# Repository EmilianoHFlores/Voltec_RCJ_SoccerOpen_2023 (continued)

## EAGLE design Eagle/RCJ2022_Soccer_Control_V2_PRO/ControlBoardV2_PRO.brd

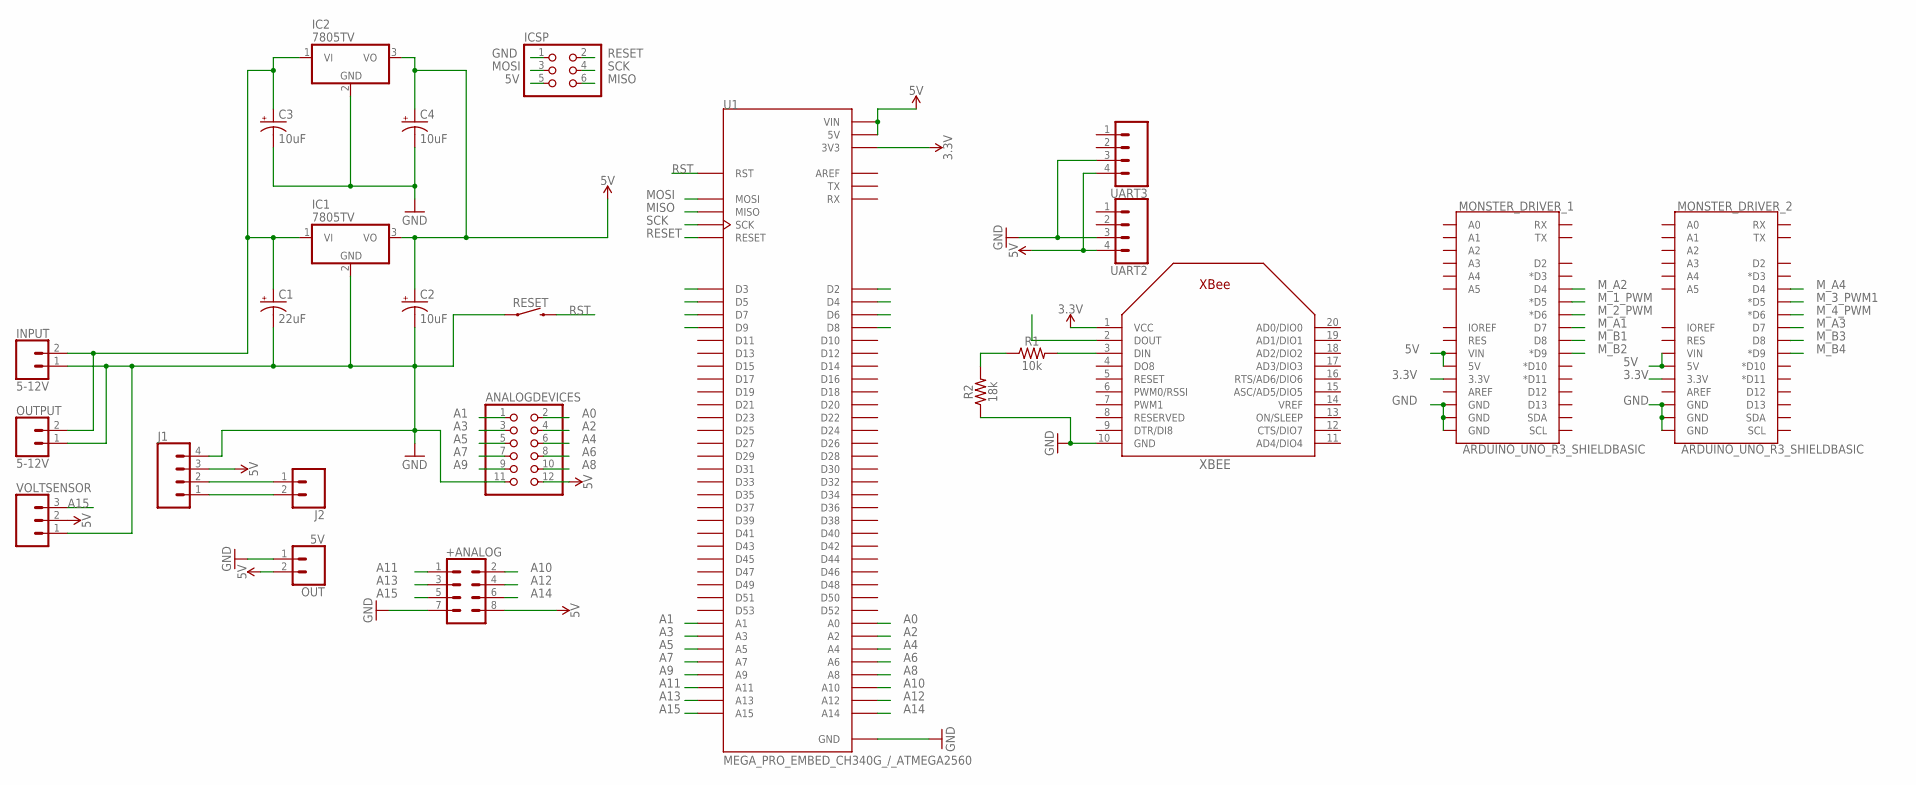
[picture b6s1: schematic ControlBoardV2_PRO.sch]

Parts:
+ANALOG: CONN_04X2; 2X4
ANALOGDEVICES: PINHD-2X6; 2X06
C1: 22uF; E2,5-5
C2, C3, C4: 10uF; E2,5-5
IC1, IC2: 7805TV; TO220V
ICSP: PINHD-2X3; 2X03
INPUT: 5-12V; SCREWTERMINAL-3.5MM-2
J1: CONN_04; 1X04
J2: CONN_02; 1X02
MONSTER_DRIVER_1, MONSTER_DRIVER_2: ARDUINO_UNO_R3_SHIELDBASIC; UNO_R3_SHIELD
OUT: 5V; SCREWTERMINAL-3.5MM-2
OUTPUT: 5-12V; SCREWTERMINAL-3.5MM-2
R1: 10k; AXIAL-0.3
R2: 18k; AXIAL-0.3
RESET: MOMENTARY-SWITCH-SPST-PTH-6.0MM; TACTILE_SWITCH_PTH_6.0MM
U1: MEGA_PRO_EMBED_CH340G_/_ATMEGA2560; MODULE_MEGA_PRO_EMBED_CH340G_/_ATMEGA2560
UART2, UART3: CONN_04; 1X04
VOLTSENSOR: CONN_03; 1X03
XBEE: XBEE

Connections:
3.3V: MONSTER_DRIVER_1.3.3V, MONSTER_DRIVER_2.3.3V, U1.3V3_1 (3V3), U1.3V3_2 (3V3), XBEE.1 (VCC)
5V: +ANALOG.8, ANALOGDEVICES.12, C2.+, C4.+, IC1.3 (VO), IC2.3 (VO), ICSP.5, J1.3, MONSTER_DRIVER_1.5V, MONSTER_DRIVER_1.VIN, MONSTER_DRIVER_2.5V, MONSTER_DRIVER_2.VIN, OUT.2, U1.5V_1 (5V), U1.5V_2 (5V), U1.5V_3 (5V), U1.VIN_1 (VIN), U1.VIN_2 (VIN), UART2.4, UART3.4, VOLTSENSOR.2
A0: ANALOGDEVICES.2, U1.A0
A1: ANALOGDEVICES.1, U1.A1
A2: ANALOGDEVICES.4, U1.A2
A3: ANALOGDEVICES.3, U1.A3
A4: ANALOGDEVICES.6, U1.A4
A5: ANALOGDEVICES.5, U1.A5
A6: ANALOGDEVICES.8, U1.A6
A7: ANALOGDEVICES.7, U1.A7
A8: ANALOGDEVICES.10, U1.A8
A9: ANALOGDEVICES.9, U1.A9
A10: +ANALOG.2, U1.A10
A11: +ANALOG.1, U1.A11
A12: +ANALOG.4, U1.A12
A13: +ANALOG.3, U1.A13
A14: +ANALOG.6, U1.A14
A15: +ANALOG.5, U1.A15, VOLTSENSOR.3
GND: +ANALOG.7, ANALOGDEVICES.11, C1.-, C2.-, C3.-, C4.-, IC1.2 (GND), IC2.2 (GND), ICSP.1, INPUT.1, J1.4, MONSTER_DRIVER_1.GND@0 (GND), MONSTER_DRIVER_1.GND@1 (GND), MONSTER_DRIVER_1.GND@2 (GND), MONSTER_DRIVER_2.GND@0 (GND), MONSTER_DRIVER_2.GND@1 (GND), MONSTER_DRIVER_2.GND@2 (GND), OUT.1, OUTPUT.1, R2.P$1 (1), RESET.1, U1.GND_1 (GND), U1.GND_2 (GND), U1.GND_3 (GND), UART2.3, UART3.3, VOLTSENSOR.1, XBEE.10 (GND)
MISO: ICSP.6, U1.MISO
MISO1: U1.D4
MISO2: U1.D5
MOSI: ICSP.3, U1.MOSI
MOSI1: U1.D2
MOSI2: U1.D3
M_1_PWM: MONSTER_DRIVER_1.D5 (*D5)
M_2_PWM: MONSTER_DRIVER_1.D6 (*D6)
M_3_PWM1: MONSTER_DRIVER_2.D5 (*D5)
M_4_PWM: MONSTER_DRIVER_2.D6 (*D6)
M_A1: MONSTER_DRIVER_1.D7
M_A2: MONSTER_DRIVER_1.D4
M_A3: MONSTER_DRIVER_2.D7
M_A4: MONSTER_DRIVER_2.D4
M_B1: MONSTER_DRIVER_1.D8
M_B2: MONSTER_DRIVER_1.D9 (*D9)
M_B3: MONSTER_DRIVER_2.D8
M_B4: MONSTER_DRIVER_2.D9 (*D9)
unnamed: R1.P$1 (1), R2.P$2 (2)
unnamed: R1.P$2 (2), XBEE.3 (DIN)
unnamed: C1.+, C3.+, IC1.1 (VI), IC2.1 (VI), INPUT.2, OUTPUT.2
unnamed: J1.1, J2.2
unnamed: J1.2, J2.1
RESET: ICSP.2, U1.RESET
RESET1: U1.D8
RESET2: U1.D9
RST: RESET.3 (2), U1.RST
SCK: ICSP.4, U1.SCK
SCK1: U1.D6
SCK2: U1.D7

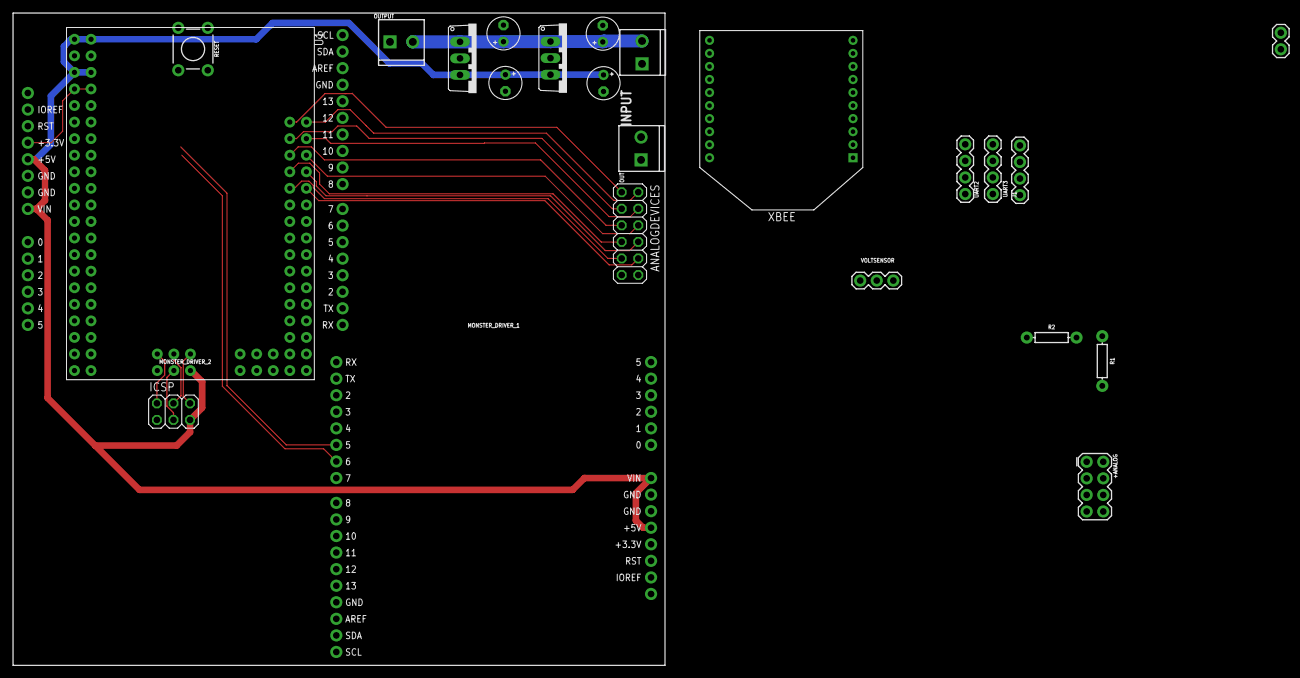
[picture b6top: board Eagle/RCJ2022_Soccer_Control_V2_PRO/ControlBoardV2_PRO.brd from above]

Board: 2 copper layers, 100.0 x 100.0 mm, 24 parts (0 on the bottom side), 29 nets.

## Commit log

2023-02-26 Added READMEs and Folders
2023-02-26 Added Eagle boards and structure folders
2023-03-02 First commit (Arduino files)
2023-03-02 First commit (openMV files)
2023-03-04 Added Eagle PCBs
    V1 and V2 of main board, tutorial board.
2023-03-04 Rename sketch_jan22a.ino to main.ino
2023-04-06 Cambios pre-regional
2023-04-13 Pruebas Xbee
2023-04-14 Camera calibration scripts
2023-04-14 README.md actualizado
2023-04-14 Librería de motores actualizada para monster drivers
2023-04-17 Added program to convert LSM readings to navx-like
2023-04-17 Uploaded Boards
2023-04-17 Added NAVX and LSMtoNavx examples
2023-04-23 Prototipo robot atacante}
2023-04-23 Últimos cambios, prototipo de robot atacante estable
2023-04-25 Robot atacante estable
2023-05-01 Cambios TMR 2023
2023-05-14 Nuevo sistema de comunicación entre Arduino y OpenMV (beta)
2023-05-18 Motor brushless prueba
2023-05-23 Primera base para 4to modelo
2023-05-27 Nueva librería de OpenMV y rediseño de estrategias
2023-06-03 Xbee y robot defensor funcional
2023-06-03 Xbee y robot defensa funcional
2023-06-04 Emulador de robot (Xbee)
2023-06-24 Prototipos funcionales de ambos robots para mundial rcj 2023
2023-06-24 Error de memoria dinámica de variables locales resuelto
2023-06-27 Programación considerando Kicker
2023-07-01 Versión final Robocup2023
